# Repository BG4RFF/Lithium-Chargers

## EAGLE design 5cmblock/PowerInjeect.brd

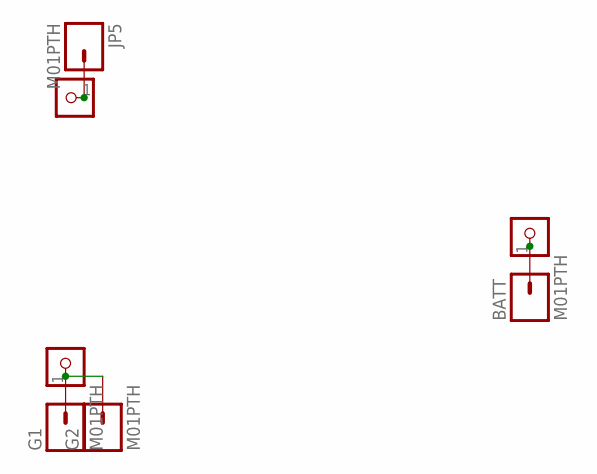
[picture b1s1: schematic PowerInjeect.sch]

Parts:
BATT: M01PTH; 1X01
G1, G2: M01PTH; 1X01
J2, J3, J6: CON_HEADER_1X01-PTH_10_17; M1X2_10_17
JP5: M01PTH; 1X01

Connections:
unnamed: G1.1, G2.1, J3.1
unnamed: J2.1, JP5.1
unnamed: BATT.1, J6.1

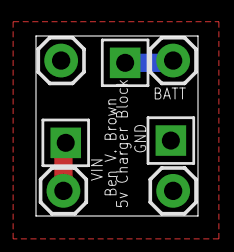
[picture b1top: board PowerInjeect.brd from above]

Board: 2 copper layers, 9.0 x 10.0 mm, 7 parts (0 on the bottom side), 3 nets.

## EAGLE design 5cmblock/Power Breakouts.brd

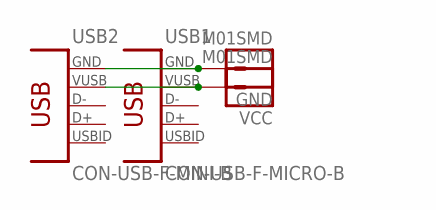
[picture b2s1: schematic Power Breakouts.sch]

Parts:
GND: M01SMD; LUXEON-PAD
USB1: CON-USB-F-MICRO-B; CONN_USB_MICRO-B
USB2: CON-USB-F-MINI-B; CONN_USB_MINI-B
VCC: M01SMD; LUXEON-PAD

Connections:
unnamed: GND.P$1, USB1.P5 (GND), USB2.GND
unnamed: USB1.P1 (VUSB), USB2.VUSB, VCC.P$1

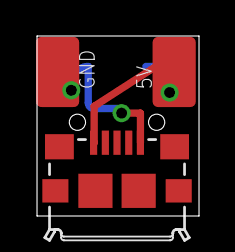
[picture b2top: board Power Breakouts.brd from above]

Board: 2 copper layers, 9.0 x 10.0 mm, 4 parts (1 on the bottom side), 2 nets.

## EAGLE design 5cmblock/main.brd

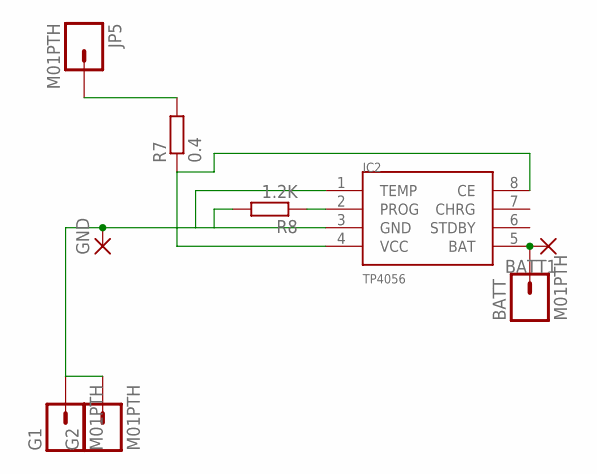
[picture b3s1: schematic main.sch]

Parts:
BATT: M01PTH; 1X01
BATT1: SMD2; SMD1,27-2,54
G1, G2: M01PTH; 1X01
GND: SMD2; SMD1,27-2,54
IC2: TP4056; SOP-8
JP5: M01PTH; 1X01
R7: 0.4; M0805
R8: 1.2K; R0603

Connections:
unnamed: BATT.1, BATT1.1, IC2.5 (BAT)
unnamed: G1.1, G2.1, GND.1, IC2.1 (TEMP), IC2.3 (GND), R8.2
unnamed: JP5.1, R7.2
unnamed: IC2.4 (VCC), IC2.8 (CE), R7.1
unnamed: IC2.2 (PROG), R8.1

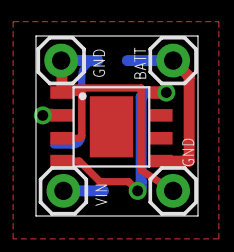
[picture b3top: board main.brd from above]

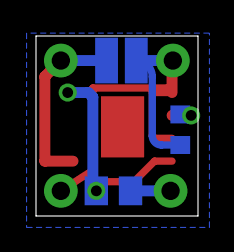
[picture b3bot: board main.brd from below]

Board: 2 copper layers, 9.0 x 10.0 mm, 9 parts (4 on the bottom side), 5 nets.

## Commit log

2014-07-17 :octocat: Added .gitattributes & .gitignore files
2014-07-18 Add Mini Lithium
    These are designed to stack to provide the chargers at any amp rate
2014-07-18 Add power layers

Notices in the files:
parts and their libraries:
SparkFun-Connectors: Licensing: Creative Commons ShareAlike 4.0 International - https://creativecommons.org/licenses/by-sa/4.0
